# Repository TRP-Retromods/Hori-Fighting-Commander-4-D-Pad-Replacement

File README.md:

# Hori-Fighting-Commander-4-D-Pad-Replacement
Replacement of the D-Pad for the Hori Fighting Commander 4 with microswitches.

You need :
- The top and bottom 3D parts,
- PCB should be in 1.6mm,
- 4 Microswitches (recommand omron D2FC-FK(50M)),
- Male 5 Pin JST PH Connector,

[https://www.printables.com/model/163826-hori-fighting-commander-4-dpad-replacement](https://www.printables.com/model/163826-hori-fighting-commander-4-dpad-replacement)

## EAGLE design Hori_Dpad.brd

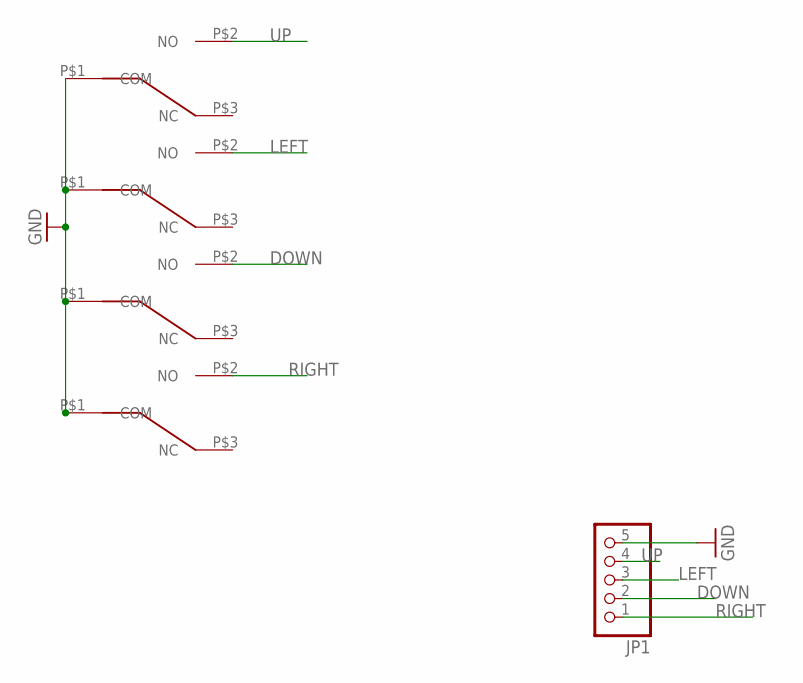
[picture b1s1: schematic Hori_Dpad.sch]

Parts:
DOWN: OMRON_D2FC-F-7N; D2FC-F-K
JP1: PINHD-1X05_2.00; 1X05M
LEFT: OMRON_D2FC-F-7N; D2FC-F-K
RIGHT: OMRON_D2FC-F-7N; D2FC-F-K
UP: OMRON_D2FC-F-7N; D2FC-F-K

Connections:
DOWN: DOWN.P$2 (NO), JP1.2
GND: DOWN.P$1 (COM), JP1.5, LEFT.P$1 (COM), RIGHT.P$1 (COM), UP.P$1 (COM)
LEFT: JP1.3, LEFT.P$2 (NO)
RIGHT: JP1.1, RIGHT.P$2 (NO)
UP: JP1.4, UP.P$2 (NO)

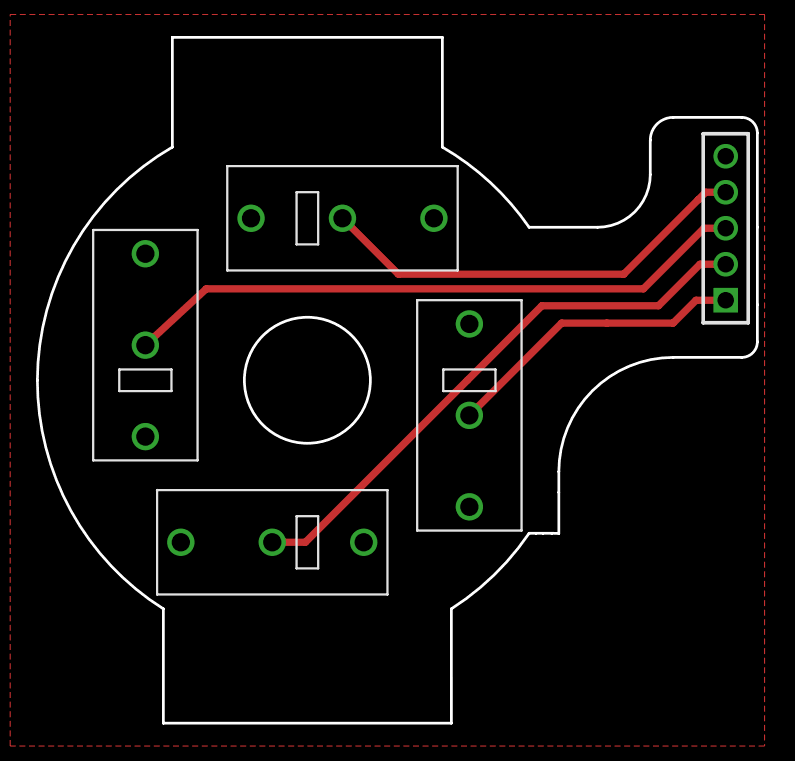
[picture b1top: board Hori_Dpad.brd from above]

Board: 2 copper layers, 40.0 x 38.1 mm, 6 parts (1 on the bottom side), 5 nets.

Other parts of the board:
U$1: LOGO

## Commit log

2020-01-26 Add STL files for 3D Parts, Eagle and Gerber files for PCB.
